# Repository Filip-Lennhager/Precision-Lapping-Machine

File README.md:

# Precision Lapping Machine

This project was created by:

+ Filip Lennhager, `filip@lennhager.se`
+ Filip Karlsson
+ Albin Magnusson
+ Ali Halbastian Abdulla
+ Anton Meuller
+ Christian Mallqui Castro
+ Toni Carillo

## Table of Contents

1. [Prototype](#prototype)
2. [Disc and Fixation](#disc-and-fixation)
3. [Gearbox](#gearbox)
4. [Control System](#control-system)
    + [PCB](#pcb)
        + [Electrical Schematic](#electrical-schematic)
        + [Physical Schematic](#electrical-schematic)
    + [Code](#code)

## Prototype

CAD model of the prototype:

## Disc and Fixation

## Gearbox

## Control System

### PCB

#### Electrical Schematic

An overview of the electrical schematic can be found in the file: [`Precision-Lapping-Machine-1.png`](Control_System/PCB/Electrical_Schematic/Precision-Lapping-Machine-1.png):

#### Physical Schematic

Schematic of PCB with physical component placement:

Gerber and drill files for pcb fabrication:

.png)
.png)
.png)
.png)
.png)
.png)
.png)
.png)
.png)

### Code

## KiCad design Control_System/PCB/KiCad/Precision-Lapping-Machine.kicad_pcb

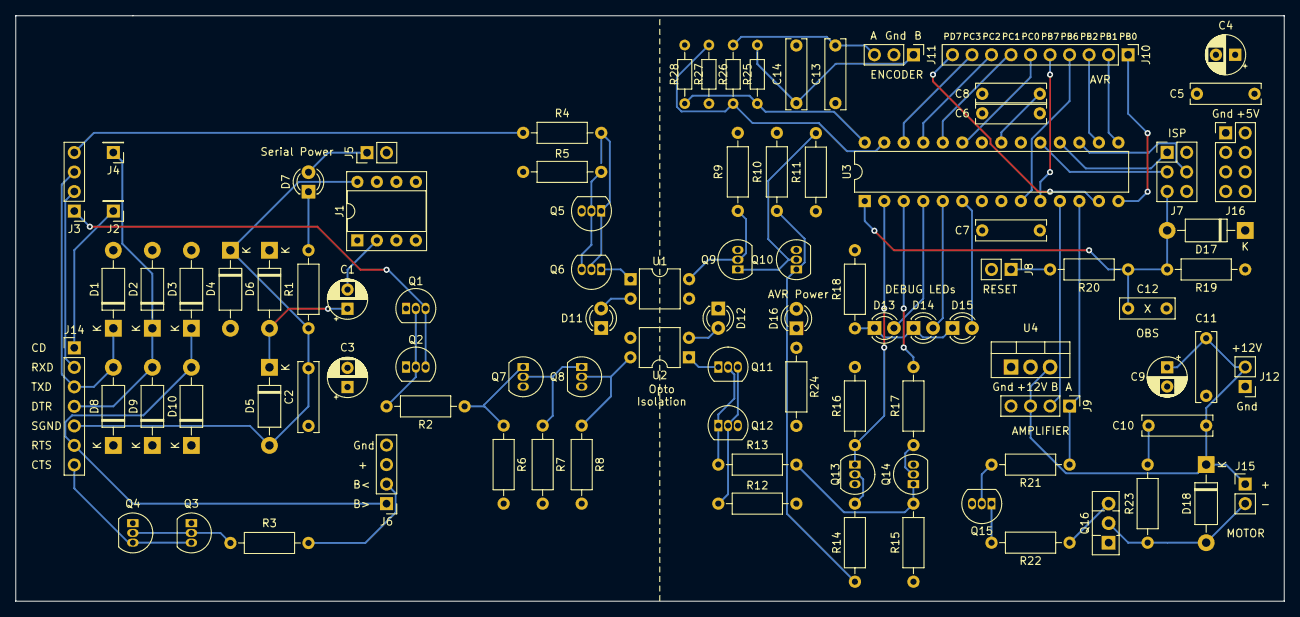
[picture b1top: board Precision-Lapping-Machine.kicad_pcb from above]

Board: 4 copper layers, 165.1 x 76.2 mm, 95 parts (0 on the bottom side), 72 nets.

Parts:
C1, C3: 10u; CP_Radial_D5.0mm_P2.50mm
C2: 1u; C_Rect_L9.0mm_W2.5mm_P7.50mm_MKT
C4, C9: 1u; CP_Radial_D5.0mm_P2.50mm
C5, C11: 1n; C_Rect_L9.0mm_W2.5mm_P7.50mm_MKT
C6, C7, C8, C10, C13, C14: 100n; C_Rect_L9.0mm_W2.5mm_P7.50mm_MKT
C12: 100n (OBS); C_Rect_L7.0mm_W2.5mm_P5.00mm
D1, D2, D3, D5, D6, D8, D9, D10: D_DO-41_SOD81_P10.16mm_Horizontal
D4: 9V; D_DO-41_SOD81_P10.16mm_Horizontal
D7, D11, D12: LED; LED_D3.0mm
D13: LED1; LED_D3.0mm
D14: LED2; LED_D3.0mm
D15: LED3; LED_D3.0mm
D16: LEDP; LED_D3.0mm
D17: ESD; D_DO-41_SOD81_P10.16mm_Horizontal
D18: 1N4004; D_DO-41_SOD81_P10.16mm_Horizontal
J1: DIP8; DIP-8_W7.62mm_Socket
J2, J4: SIP1; PinHeader_1x01_P2.54mm_Vertical
J3, J6, J9: SIP4; PinHeader_1x04_P2.54mm_Vertical
J5, J15: SIP2; PinHeader_1x02_P2.54mm_Vertical
J7: AVR-ISP; PinHeader_2x03_P2.54mm_Vertical
J8: RESET; PinHeader_1x02_P2.54mm_Vertical
J10: Conn_01x10; PinHeader_1x10_P2.54mm_Vertical
J11: SIP3; PinHeader_1x03_P2.54mm_Vertical
J12: Gnd +12V; PinHeader_1x02_P2.54mm_Vertical
J14: SIP7; PinHeader_1x07_P2.54mm_Vertical
J16: Gnd +5V; PinHeader_2x04_P2.54mm_Vertical
Q1, Q3, Q7, Q8, Q9, Q10, Q13, Q14: BC547; TO-92_Inline
Q2, Q4, Q5, Q6, Q11, Q12, Q15: BC557; TO-92_Inline
Q16: BD179; TO-126-3_Vertical
R1, R21: 3K3; R_Axial_DIN0207_L6.3mm_D2.5mm_P10.16mm_Horizontal
R2, R3, R22, R23: 100; R_Axial_DIN0207_L6.3mm_D2.5mm_P10.16mm_Horizontal
R4, R8, R9, R13, R14, R17, R19: 10K; R_Axial_DIN0207_L6.3mm_D2.5mm_P10.16mm_Horizontal
R5, R12, R18, R20, R24: 330; R_Axial_DIN0207_L6.3mm_D2.5mm_P10.16mm_Horizontal
R6, R7, R10, R11, R15, R16: 100K; R_Axial_DIN0207_L6.3mm_D2.5mm_P10.16mm_Horizontal
R25, R26, R27, R28: 10k; R_Axial_DIN0204_L3.6mm_D1.6mm_P7.62mm_Horizontal
U1, U2: PC817; DIP-4_W7.62mm
U3: ATmega88; DIP-28_W7.62mm
U4: L7805CV; TO-220-3_Vertical

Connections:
+5V: C4.1, C5.2, C6.2, C7.2, D16.2 (A), D17.1 (K), J7.2 (VCC), J16.5, J16.6, J16.7, J16.8, Q12.3 (E), Q15.3 (E), R9.1, R10.1, R11.1, R12.2, R15.1, R16.2, R19.1, R27.2, R28.1, U3.7 (VCC), U3.20 (AVCC), U4.2 (VO)
+12V: C9.1, C10.1, C11.2, D18.1 (K), J9.3, J12.2, J15.1, U4.3 (VI)
/AVR/IntA: R26.2, R27.1, U3.27 (PC4)
/AVR/IntB: R25.2, R28.2, U3.28 (PC5)
/AVR/PWMA: J9.1, R21.1, U3.12 (PD6)
/AVR/PWMB: J9.2, U3.11 (PD5)
/AVR/Rx: Q13.1 (C), R16.1, U3.2 (PD0)
/AVR/Tx: R17.2, U3.3 (PD1)
/Amplifier/Motor-: D18.2 (A), J15.2, Q16.2 (C), R23.1
/Inverter/VinL: Q10.1 (C), R10.2, R14.1
/Inverter/VoutL: Q14.1 (C), R13.1, R15.2
/OptoIsolation/Serial_Gnd: C2.2, C3.2, D1.2 (A), D2.2 (A), D3.2 (A), D4.2 (A), D11.1 (K), J1.3, J1.5, J6.4, Q2.1 (C), Q4.1 (C), Q7.3 (E), Q8.3 (E), U2.3
/OptoIsolation/Vcc: C3.1, D6.1 (K), D8.1 (K), D9.1 (K), D10.1 (K), J5.2, J6.3, Q1.1 (C), Q3.1 (C), Q5.3 (E), R5.1, R6.2, R7.2, R8.2
/OptoIsolation/VinL: J3.4, R4.2
/OptoIsolation/VoutL: Q7.1 (C), R2.1, R6.1
/Serial/CD: J2.1, J14.1
/Serial/CTS: J14.7, Q3.3 (E), Q4.3 (E)
/Serial/DTR: D2.1 (K), D9.2 (A), J4.1, J14.4
/Serial/RTS: D3.1 (K), D10.2 (A), J6.1, J14.6
/Serial/RXD: J3.2, J14.2
/Serial/SGND: C2.1, D4.1 (K), D5.2 (A), J1.8, J14.5, R1.2
/Serial/TXD: D1.1 (K), D8.2 (A), J3.3, J14.3
GND: C4.2, C5.1, C6.1, C7.1, C8.1, C9.2, C11.1, C12.1, C13.1, C14.2, D12.1 (K), J7.6 (GND), J8.2, J9.4, J11.2, J12.1, J16.1, J16.2, J16.3, J16.4, Q9.3 (E), Q10.3 (E), Q13.3 (E), Q14.3 (E), Q16.1 (E), R18.2, R24.2, U1.3, U3.8 (GND), U3.22 (GND), U4.1 (GND)
unnamed: C10.2, R23.2
unnamed: C1.1, D5.1 (K), D6.2 (A)
unnamed: D7.2 (A), J5.1
unnamed: D7.1 (K), R1.1
unnamed: D11.2 (A), U1.2
unnamed: D12.2 (A), U2.2
unnamed: D13.2 (A), U3.4 (PD2)
unnamed: D13.1 (K), D14.1 (K), D15.1 (K), R18.1
unnamed: D14.2 (A), U3.5 (PD3)
unnamed: D15.2 (A), U3.6 (PD4)
unnamed: D16.1 (K), R24.1
unnamed: C12.2, D17.2 (A), J7.5 (~RST), R19.2, R20.1, U3.1 (~RESET/PC6)
unnamed: C1.2, J1.2
unnamed: J3.1, Q1.3 (E), Q2.3 (E)
unnamed: J6.2, R3.1
unnamed: J7.1 (MISO), U3.18 (PB4)
unnamed: J7.4 (MOSI), U3.17 (PB3)
unnamed: J7.3 (SCK), U3.19 (PB5)
unnamed: J8.1, R20.2
unnamed: J10.1, U3.14 (PB0)
unnamed: J10.2, U3.15 (PB1)
unnamed: J10.3, U3.16 (PB2)
unnamed: J10.4, U3.9 (XTAL1/PB6)
unnamed: J10.5, U3.10 (XTAL2/PB7)
unnamed: J10.6, U3.23 (PC0)
unnamed: J10.7, U3.24 (PC1)
unnamed: J10.8, U3.25 (PC2)
unnamed: J10.9, U3.26 (PC3)
unnamed: J10.10, U3.13 (PD7)
unnamed: C14.1, J11.1, R25.1
unnamed: C13.2, J11.3, R26.1
unnamed: Q1.2 (B), Q2.2 (B), R2.2
unnamed: Q3.2 (B), Q4.2 (B), R3.2
unnamed: Q5.2 (B), Q6.3 (E), R5.2
unnamed: Q5.1 (C), Q6.2 (B), R4.1
unnamed: Q6.1 (C), U1.1
unnamed: Q7.2 (B), Q8.1 (C), R7.1
unnamed: Q8.2 (B), R8.1, U2.4
unnamed: Q9.2 (B), R9.2, U1.4
unnamed: Q9.1 (C), Q10.2 (B), R11.2
unnamed: Q11.2 (B), Q12.1 (C), R13.2
unnamed: Q11.1 (C), U2.1
unnamed: Q11.3 (E), Q12.2 (B), R12.1
unnamed: Q13.2 (B), R14.2
unnamed: Q14.2 (B), R17.1
unnamed: Q15.2 (B), R21.2
unnamed: Q15.1 (C), R22.2
unnamed: Q16.3 (B), R22.1
unnamed: C8.2, U3.21 (AREF)

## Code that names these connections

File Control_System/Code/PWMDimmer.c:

// Includes and definitions

#define F_CPU 1000000

#include <avr/io.h>
#include <avr/interrupt.h>
#include <util/delay.h>
#include <string.h>

// Function declaration
int init_LEDs(void);
int set_LED(int position, int value);

int AB=3;
uint8_t duty;

int main(void) {
	
	sei();    // set global interrupt flag -> enable ALL interrupts (but those that are masked won't do anything)
	//set_LED(1,1);
	setup_INTs();
	setup_PWM();
	//set_LED(2,1);
	duty=100;
	update_PWM();
	while(1) {
	
	_delay_ms(200);

		}
	
	return 0;
}

	
int setup_PWM(void) {
	
	DDRD |= ((1<<DDD5)|(1<<DDD6));	//Set PIND5 and PIND6 as outputs
	TCCR0A |= 0b11100011;			//Configure fast PWM mode, non-inverted output on OCB 4 and inverted output on OCA 3 amplifier conected to oca3
	TCCR0B |= 0x01;					//Internal clock selector, no prescaler
	return 1;
}


int setup_INTs(void) {

	PCMSK0 = (1<<PCINT1)|(1<<PCINT2); //PB1 and PB2
	PCICR = (1 << PCIE0);
	return 1;
}


int encoder_read(void) {
    
	//encoder read: function that reads wether the encoder is moving one way or the other: 1 or -1
	int res; //result, 1 or -1 depending on direction
	int An; //Channel A new value fo the encoder
	int Bn; //Channel B new value of the encoder
	int AB_new;
	
	//Read pins and assign values to vbles A2 and B2 (new value after interruption)
	//Chanel A connected to PD2 and chanel B connected to PD3
	An = PINB & (1<<PINB1);
	Bn = PINB & (1<<PINB2);
	
	AB_new=(An|Bn)>>PINB1;
	
	//Make the computations to guess the direction in which the encoder is moving
	switch (AB){
		case 3 : /*AB new up*/  if (AB_new == 2) res=1; /*B moves*/ else  res = 2; break; /* A moves */		
		case 2 : /*A up B down*/if (AB_new == 0) res=1; /*B moves*/ else  res = 2; break; /* A moves */
		case 1 : /*A down B up*/if (AB_new == 3) res=1; /*B moves*/ else  res = 2; break; /* A moves */
		case 0 : /*AB new down*/if (AB_new == 1) res=1; /*B moves*/ else  res = 2; break; /* A moves */
	}
	
	//Set led 1 on if res=1 and led 2 on if res=2, or led 3 on in other case (for debuging)
	
	//Update global variables with new encoder value
	AB = AB_new;
	
	return res;
}

ISR(PCINT0_vect)
{

	cli(); 
	int dir = encoder_read();
	if (dir == 1 && duty < 255 ) {
    duty++;
    }
	else if (dir == 2 && duty > 0) {
    duty--;
    }
	update_PWM();
	sei();
}

int update_PWM(void)
{
	/* Making sure the duty is within the range */
	if (duty < 0) {
         OCR0A = 0;
    }
	else if (duty > 255) {
        OCR0A = 255;
    } else {
        OCR0A = duty;
    }
	return 1;
}

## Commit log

2023-05-23 Added PCB KiCad Project
2023-05-23 README.MD plot test
2023-05-23 Updated Electrical Schematic for PCB in README.md
2023-05-23 Added Code for PWM control with dimmer
2023-05-24 Added Gearbox CAD files
2023-05-24 Added CAD for arm and self-self aligning weight
2023-05-24 Added gearbox img
2023-05-24 Revert "Added gearbox img"
    This reverts commit de685fda34cf269d301c6a88953607c8e0699a98.
2023-05-24 Added Gerber files and PCB schematic
2023-05-26 Added disc CAD and prototype images
2023-05-26 Added gerber plots
2023-05-26 refactoring
2023-05-26 Added PCB CAD img
